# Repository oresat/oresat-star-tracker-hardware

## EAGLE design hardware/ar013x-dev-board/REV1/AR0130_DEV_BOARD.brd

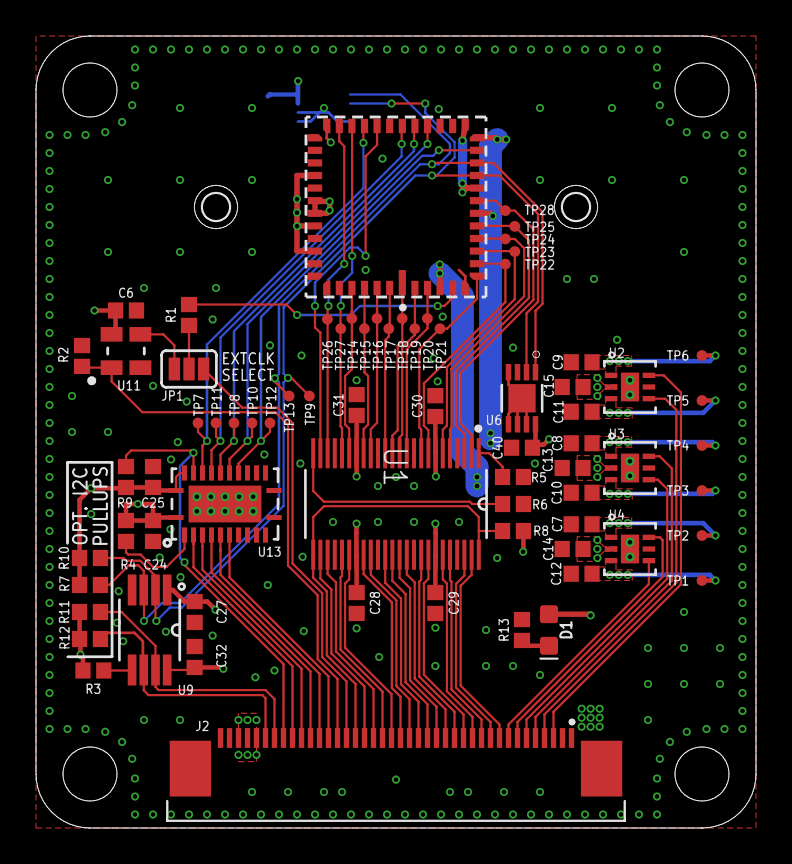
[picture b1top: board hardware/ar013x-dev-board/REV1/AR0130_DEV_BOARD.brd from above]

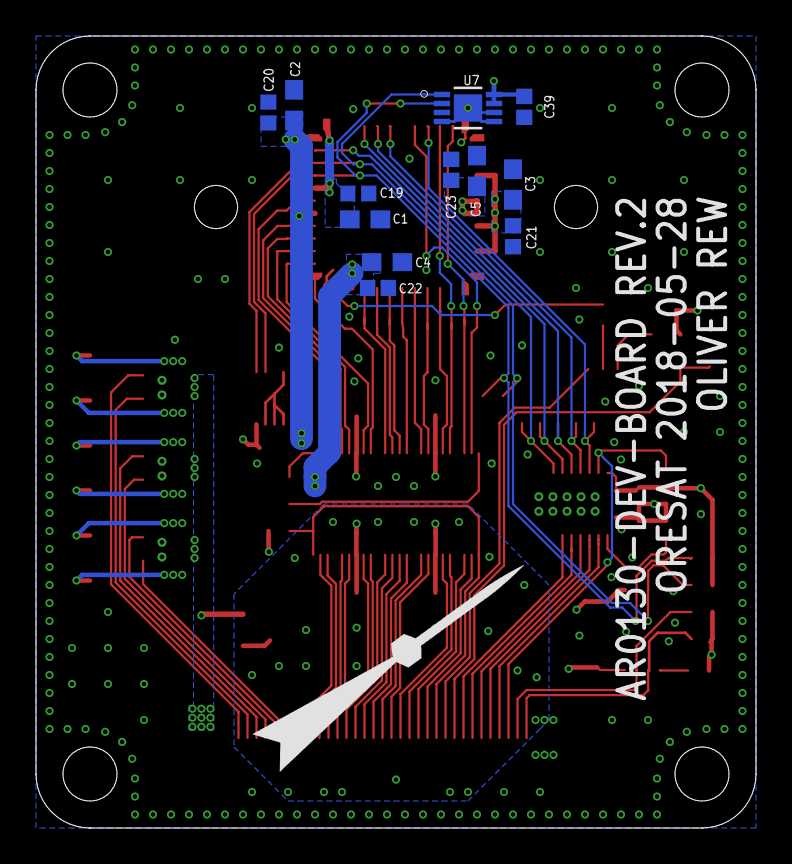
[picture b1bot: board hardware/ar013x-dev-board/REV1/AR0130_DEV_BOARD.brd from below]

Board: 4 copper layers, 40.0 x 44.0 mm, 86 parts (13 on the bottom side), 72 nets.

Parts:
C1, C2, C3, C4, C5: 10uF; 0603
C6: 10nF; 0402
C7, C8, C9, C10, C11, C12, C13, C14, C15: 1.0uF; 0402
C19, C20, C21, C22, C23, C24, C25, C27, C28, C29, C30, C31, C32, C39, C40: 0.1uF; 0402
D1: LED-0603
J2: 4-1734592-04-1734592-0; TE_4-1734592-0
JP1: CLKSEL; SJ_3_PASTE1&2
R1: 100; 0402
R2, R3, R4, R5, R6, R7, R8, R9, R10, R11, R12: 10k; 0402
R13: 1k; 0402
TP1, TP2, TP3, TP4, TP5, TP6, TP7, TP8, TP9, TP10, TP11, TP12, TP13, TP14, TP15, TP16, TP17, TP18, TP19, TP20, TP21, TP22, TP23, TP24, TP25, TP26, TP27, TP28: TPTP06R; TP06R
U1: SN74AVCB164245VR; DGV48
U2, U3: TPS71928-28DRVT; DRV6_1P6X1
U4: TPS71818-33DRVT; DRV6_1P6X1
U6, U7: MCP9808T-E/MCDFN8_2X3MC-M; DFN8_2X3MC-M
U9: TCA9509DGKRDGK8-M; DGK8-M
U11: KC2520B27.0000C10E00; OSC_KYOCERA_KC2520B
U13: SN74AVCH8T245RHLR; RHL24_4P05X2P05
U$1: M12-LENS-MOUNT
U$2: AR0130CSSM00SPCA0−DRBR1-847AC-ILCC; AR0130CSSM00SPCA0−DRBR1-847AB
U$3: PSAS_LOGO_15X15

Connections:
1.8V: C1.1, C7.1, C19.1, TP2.TP, U4.1, U$2.14, U$2.19
2.8V: C2.1, C6.2, C8.1, C20.1, C25.1, C27.1, C30.1, C31.1, C39.1, C40.1, R7.2, R9.2, R10.1, TP4.TP, U1.7, U1.18, U3.1, U6.8, U7.7, U7.8, U9.1, U11.4, U13.23, U13.24, U$2.12, U$2.18
3.3V: C12.1, C24.1, C28.1, C29.1, C32.1, R3.2, R4.1, R8.2, R11.1, R12.2, TP1.TP, U1.31, U1.42, U4.3, U9.8, U13.1
3.3V_EN: J2.8, U4.4
5V: C13.1, C14.1, C15.1, D1.A, J2.36, J2.37, J2.38, U2.2, U3.2, U4.2
CLK_EN: J2.27, R2.2, U11.1
DE_0: J2.21, U1.30
DE_1: J2.20, U1.32
DE_2: J2.19, U1.33
DE_3: J2.18, U1.35
DE_4: J2.17, U1.36
DE_5: J2.16, U1.37
DE_6: J2.15, U1.38
DE_7: J2.14, U1.40
DE_8: J2.13, U1.41
DE_9: J2.12, U1.43
DE_10: J2.11, U1.44
DE_11: J2.10, U1.46
DI_0: TP14.TP, U1.19, U$2.45
DI_1: TP15.TP, U1.17, U$2.46
DI_2: TP16.TP, U1.16, U$2.47
DI_3: TP17.TP, U1.14, U$2.48
DI_4: TP18.TP, U1.13, U$2.1
DI_5: TP19.TP, U1.12, U$2.2
DI_6: TP20.TP, U1.11, U$2.3
DI_7: TP21.TP, U1.9, U$2.7
DI_8: TP22.TP, U1.8, U$2.8
DI_9: TP23.TP, U1.6, U$2.9
DI_10: TP24.TP, U1.5, U$2.10
DI_11: TP25.TP, U1.3, U$2.11
EXTCLK: JP1.2, R1.1
EXTCLK_E: J2.26, JP1.3
EXTCLK_I: JP1.1, U11.3
FLASH_E: J2.24, U1.26
FLASH_I: U1.23, U$2.26
GND: C1.2, C2.2, C3.2, C4.2, C5.2, C6.1, C7.2, C8.2, C9.2, C10.2, C11.2, C12.2, C13.2, C14.2, C15.2, C19.2, C20.2, C21.2, C22.2, C23.2, C24.2, C25.2, C27.2, C28.2, C29.2, C30.2, C31.2, C32.2, C39.2, C40.2, J2.1, J2.2, J2.39, J2.40, J2.S1, J2.S2, R2.1, R5.1, R6.1, R13.2, U1.4, U1.10, U1.15, U1.21, U1.28, U1.34, U1.39, U1.45, U2.5, U2.7, U2.8, U2.9, U3.5, U3.7, U3.8, U3.9, U4.5, U4.7, U4.8, U4.9, U6.4, U6.5, U6.6, U6.7, U6.9, U7.4, U7.5, U7.6, U7.9, U9.4, U11.2, U13.11, U13.12, U13.13, U13.25, U13.P$1, U13.P$2, U13.P$3, U13.P$4, U13.P$5, U13.P$6, U13.P$7, U13.P$8, U13.P$9, U13.P$10, U$2.6, U$2.25, U$2.30, U$2.35, U$2.39, U$2.44
HSYNC_E: J2.23, U1.27
HSYNC_I: TP26.TP, U1.22, U$2.29
INPUT_DRVR_EN: J2.33, R9.1, U13.22
unnamed: R1.2, U$2.5
unnamed: D1.C, R13.1
unnamed: R5.2, U1.1
unnamed: R3.1, U9.5
unnamed: R4.2, U13.2
unnamed: R6.2, U1.24
OE_BAR_E: J2.30, U13.5
OE_BAR_I: TP8.TP, U13.19, U$2.23
OUTPUT_DRVR_EN: J2.25, R8.1, U1.25, U1.48
PIXCLK_E: J2.9, U1.47
PIXCLK_I: TP28.TP, U1.2, U$2.13
RST_BAR_E: J2.28, U13.7
RST_BAR_I: TP9.TP, U13.17, U$2.17
SADDR_E: J2.31, U13.4
SADDR_I: TP11.TP, U13.20, U$2.24
SCL_E: J2.34, R12.1, U9.7
SCL_I: R7.1, TP12.TP, U6.2, U7.2, U9.2, U$2.15
SDA_E: J2.35, R11.2, U9.6
SDA_I: R10.2, TP13.TP, U6.1, U7.1, U9.3, U$2.16
STANDBY_E: J2.29, U13.6
STANDBY_I: TP10.TP, U13.18, U$2.22
TRIG_E: J2.32, U13.3
TRIG_I: TP7.TP, U13.21, U$2.27
VAA_EN: J2.3, U2.6
VAA_PIX_EN: J2.4, U2.4
VCC: C3.1, C9.1, C21.1, TP6.TP, U2.1, U$2.34, U$2.38, U$2.40
VCC_1: C4.1, C10.1, C22.1, TP3.TP, U3.3, U$2.4
VCC_2: C5.1, C11.1, C23.1, TP5.TP, U2.3, U$2.36, U$2.37
VDD18_EN: J2.7, U4.6
VDD_IO_EN: J2.5, U3.6
VDD_PLL_EN: J2.6, U3.4
VSYNC_E: J2.22, U1.29
VSYNC_I: TP27.TP, U1.20, U$2.28

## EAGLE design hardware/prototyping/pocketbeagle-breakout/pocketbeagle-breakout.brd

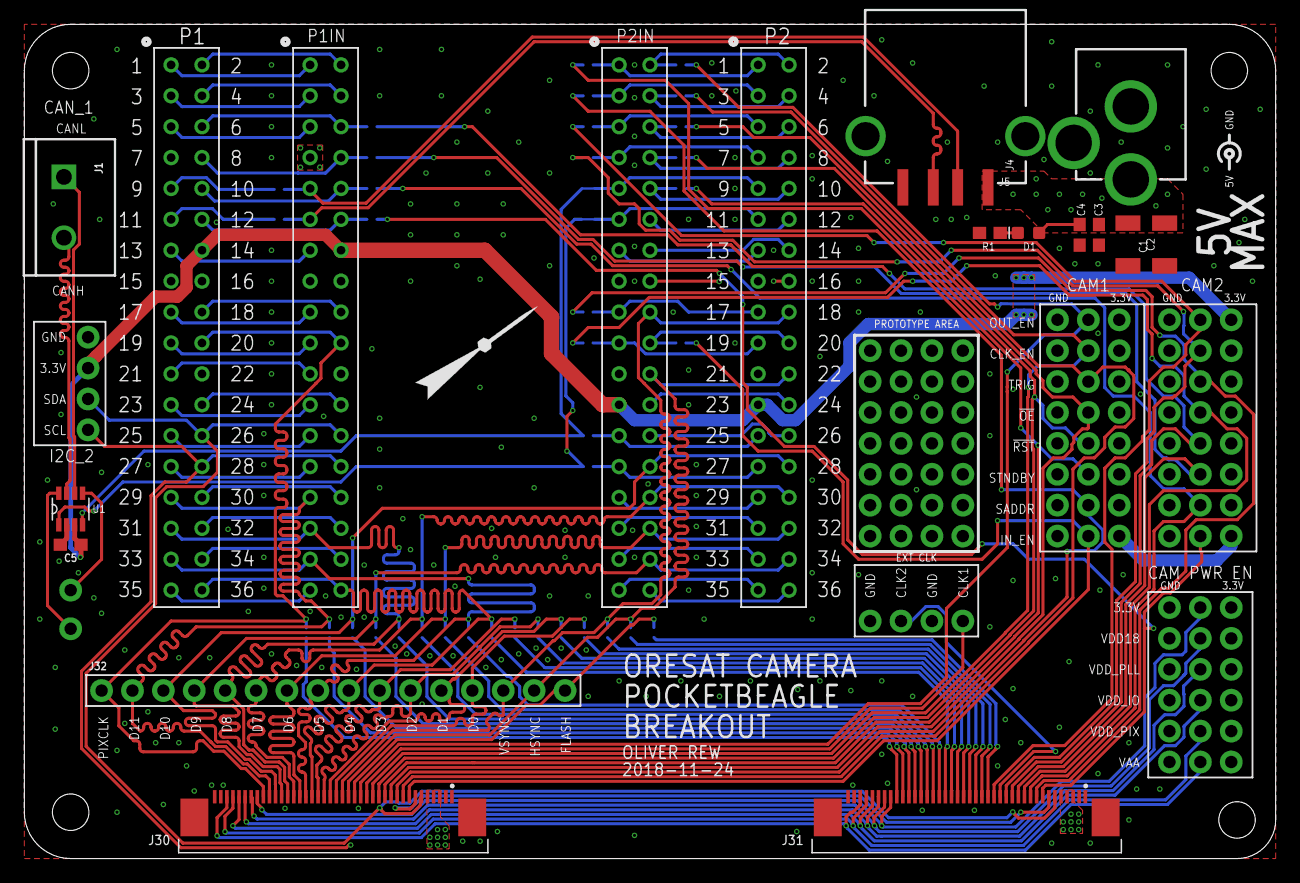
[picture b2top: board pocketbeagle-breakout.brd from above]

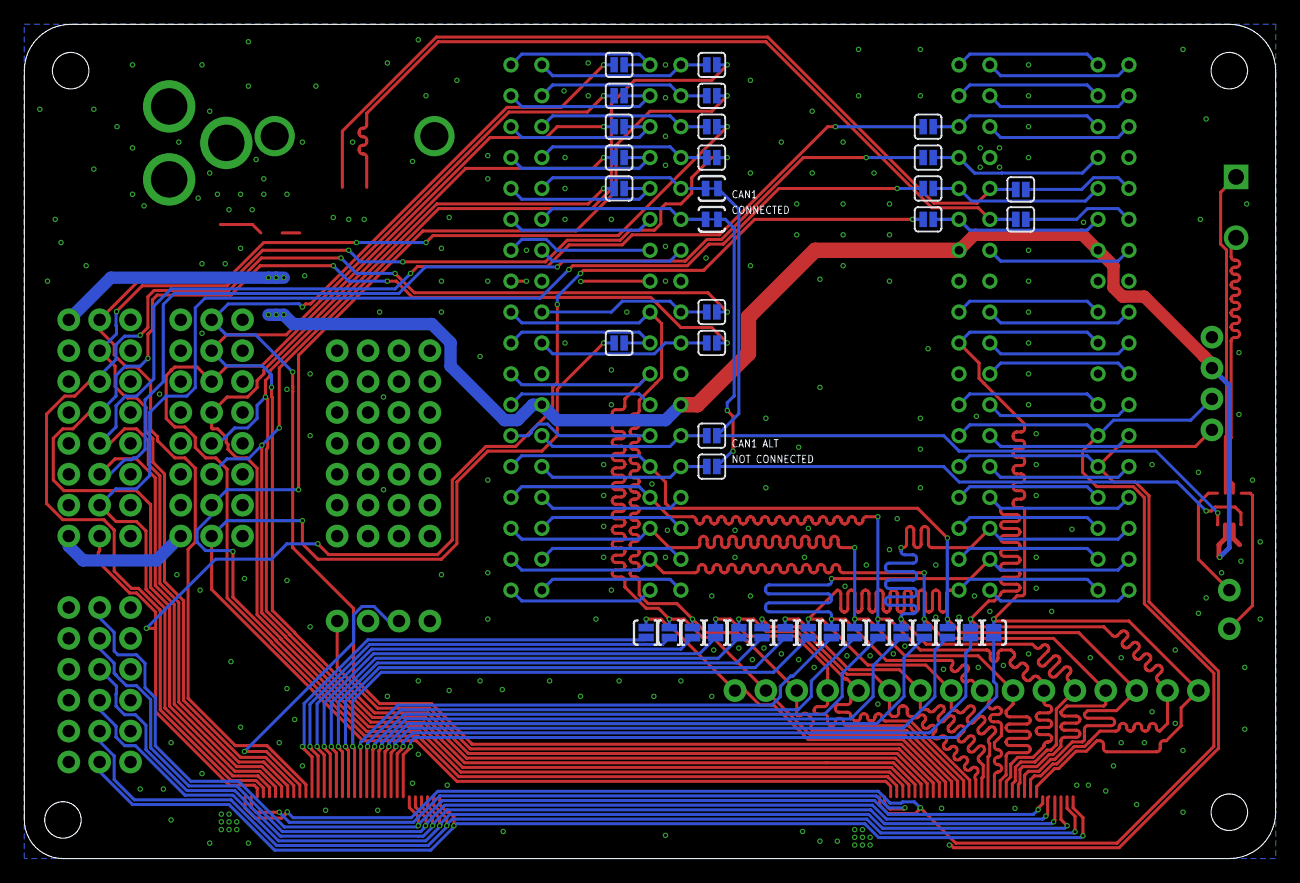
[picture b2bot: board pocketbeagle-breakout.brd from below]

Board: 4 copper layers, 102.9 x 68.6 mm, 91 parts (39 on the bottom side), 121 nets.

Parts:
C1, C2: 22UF; 1210
C3, C4, C5: 0.1uF; 0603
D1: GREEN; LED-0603
J1: SCREWTERMINAL-5MM-2
J3, J6, J7, J8, J9, J10, J11, J12, J13, J14, J15, J16, J17, J18, J20, J22, J23, J24, J25, J26, J27, J28: 1X03_NO_SILK
J4: USB_A_SMT_FEMALE; USB-A-S-SILK-FEMALE
J5: POWER_JACK; POWER_JACK_PTH
J19, J38, J39, J40, J41, J42, J43, J44, J45: 1X04_NO_SILK
J30, J31: 4-1734592-04-1734592-0; TE_4-1734592-0
J32: 1X16_NO_SILK
J36, J37: 1X01_NO_SILK
P1, P1IN, P2, P2IN: BCS-118-L-D-TE; CON36_2X18_TU_BCS
R1: 1k; 0603
SJ1, SJ2, SJ3, SJ4, SJ5, SJ6, SJ7, SJ8, SJ9, SJ10, SJ11, SJ12, SJ13, SJ14, SJ15, SJ16: SOLDERJUMPERNC2; SJ_2S-NOTRACE
SJ17, SJ18, SJ21, SJ22, SJ23, SJ24, SJ25, SJ26, SJ27, SJ28, SJ29, SJ30, SJ31, SJ32, SJ33, SJ34, SJ35, SJ36, SJ37, SJ38: SOLDERJUMPERNC; SJ_2S
SJ19, SJ20: SOLDERJUMPERTRACE; SJ_2S-TRACE
U1: TCAN330; SOT23-8_TI-DCN
U$1: PSAS_LOGO_10X10_NEW
U$2: POLARITY_SYMBOL_SMALL

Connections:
3.3V: C5.1, J3.3, J6.3, J7.3, J8.3, J9.3, J10.3, J11.3, J12.3, J13.3, J14.3, J15.3, J16.3, J17.3, J18.3, J19.2, J20.3, J22.3, J23.3, J24.3, J25.3, J26.3, J27.3, J28.3, P1.14, P1IN.14, P2.23, P2IN.23, U1.3
3.3V_EN: J17.2, J30.33, J31.33
5V: C1.1, C2.1, C3.1, C4.1, D1.A, J4.VBUS, J5.PWR, J30.3, J30.4, J30.5, J31.3, J31.4, J31.5, P1.7, P1IN.7
CAN_H: J1.2, U1.7
CAN_L: J1.1, U1.6
CAN_RX: SJ17.2, SJ19.2, U1.4
CAN_TX: SJ18.2, SJ20.2, U1.1
CLK_EN_1: J26.2, J30.14, SJ36.1
CLK_EN_2: J11.2, J31.14, SJ29.2
D0: J30.20, J32.13, SJ15.1
D1: J30.21, J32.12, SJ14.1
D2: J30.22, J32.11, SJ13.1
D3: J30.23, J32.10, SJ12.1
D4: J30.24, J32.9, P1.36, P1IN.36, SJ11.1
D5: J30.25, J32.8, P1.33, P1IN.33, SJ10.1
D6: J30.26, J32.7, P2.32, P2IN.32, SJ9.1
D7: J30.27, J32.6, P2.30, P2IN.30, SJ8.1
D8: J30.28, J32.5, P1.31, P1IN.31, SJ7.1
D9: J30.29, J32.4, P2.34, P2IN.34, SJ6.1
D10: J30.30, J32.3, P2.28, P2IN.28, SJ5.1
D11: J30.31, J32.2, P1.29, P1IN.29, SJ4.1
EXTCLK_1: J30.15, J38.4
EXTCLK_2: J31.15, J38.2
FLASH: J30.17, J32.16, SJ16.2
GND: C1.2, C2.2, C3.2, C4.2, C5.2, J3.1, J4.GND, J4.SHLD1, J4.SHLD2, J5.GND, J5.GNDBREAK, J6.1, J7.1, J8.1, J9.1, J10.1, J11.1, J12.1, J13.1, J14.1, J15.1, J16.1, J17.1, J18.1, J19.1, J20.1, J22.1, J23.1, J24.1, J25.1, J26.1, J27.1, J28.1, J30.1, J30.2, J30.39, J30.40, J30.S1, J30.S2, J31.1, J31.2, J31.39, J31.40, J31.S1, J31.S2, J38.1, J38.3, P1.15, P1.16, P1.22, P1IN.15, P1IN.16, P1IN.22, P2.15, P2.21, P2IN.15, P2IN.21, R1.2, U1.2
HSYNC: J30.18, J32.15, P2.22, P2IN.22, SJ3.1
INPUT_DRVR_EN_1: J27.2, J30.8, SJ35.2
INPUT_DRVR_EN_2: J18.2, J31.8, SJ33.1
unnamed: P2.2, P2IN.2, SJ34.1
unnamed: J31.17, SJ16.1
unnamed: J31.18, SJ3.2
unnamed: J31.19, SJ2.2
unnamed: J31.20, SJ15.2
unnamed: J31.21, SJ14.2
unnamed: J31.22, SJ13.2
unnamed: J31.23, SJ12.2
unnamed: J31.24, SJ11.2
unnamed: J31.25, SJ10.2
unnamed: J31.26, SJ9.2
unnamed: J31.27, SJ8.2
unnamed: J31.28, SJ7.2
unnamed: J31.29, SJ6.2
unnamed: J31.30, SJ5.2
unnamed: J31.31, SJ4.2
unnamed: J31.32, SJ1.2
unnamed: J36.1, U1.5
unnamed: J37.1, U1.8
unnamed: P2.9, P2IN.9, SJ19.1
unnamed: P2.11, P2IN.11, SJ20.1
unnamed: P2.25, P2IN.25, SJ17.1
unnamed: P2.27, P2IN.27, SJ18.1
unnamed: D1.C, R1.1
unnamed: P2.1, P2IN.1, SJ22.2
unnamed: P2.10, P2IN.10, SJ23.2
unnamed: P2.8, P2IN.8, SJ24.2
unnamed: P2.6, P2IN.6, SJ25.2
unnamed: P2.17, P2IN.17, SJ26.1
unnamed: P2.19, P2IN.19, SJ27.1
unnamed: P2.5, P2IN.5, SJ28.1
unnamed: P2.7, P2IN.7, SJ29.1
unnamed: P1.12, P1IN.12, SJ33.2
unnamed: P1.10, P1IN.10, SJ32.2
unnamed: P1.8, P1IN.8, SJ31.2
unnamed: P1.6, P1IN.6, SJ30.2
unnamed: P2.20, P2IN.20, SJ35.1
unnamed: P2.4, P2IN.4, SJ36.2
unnamed: P1.9, SJ37.1
unnamed: P1.11, SJ38.1
unnamed: P1.27, P1IN.27
unnamed: P1.25, P1IN.25
unnamed: P1.23, P1IN.23
unnamed: P1.21, P1IN.21
unnamed: P1.19, P1IN.19
unnamed: P1.17, P1IN.17
unnamed: P1.13, P1IN.13
unnamed: P1.5, P1IN.5
unnamed: P1.3, P1IN.3
unnamed: P1.1, P1IN.1
unnamed: P1.35, P1IN.35
unnamed: P1.34, P1IN.34
unnamed: P1.32, P1IN.32
unnamed: P1.30, P1IN.30
unnamed: P1.24, P1IN.24
unnamed: P1.18, P1IN.18
unnamed: P1.4, P1IN.4
unnamed: P2.3, P2IN.3, SJ21.2
unnamed: P1.2, P1IN.2
unnamed: P2.13, P2IN.13
unnamed: P2.29, P2IN.29
unnamed: P2.31, P2IN.31
unnamed: P2.33, P2IN.33
unnamed: P2.35, P2IN.35
unnamed: P2.12, P2IN.12
unnamed: P2.14, P2IN.14
unnamed: P2.16, P2IN.16
unnamed: P2.24, P2IN.24
unnamed: P2.26, P2IN.26
unnamed: P2.36, P2IN.36
OE_BAR_1: J24.2, J30.11, SJ24.1
OE_BAR_2: J9.2, J31.11, SJ27.2
OUTPUT_DRVR_EN_1: J28.2, J30.16, SJ34.2
OUTPUT_DRVR_EN_2: J20.2, J31.16, SJ28.2
PIXCLK: J30.32, J32.1, P1.20, P1IN.20, SJ1.1
RST_BAR_1: J23.2, J30.13, SJ23.1
RST_BAR_2: J8.2, J31.13, SJ30.1
SADDR_1: J3.2, J30.10, SJ21.1
SADDR_2: J6.2, J31.10, SJ32.1
SCL2: J19.4, J30.7, J31.7, P1.28, P1IN.28
SDA2: J19.3, J30.6, J31.6, P1.26, P1IN.26
STANDBY_1: J22.2, J30.12, SJ22.1
STANDBY_2: J7.2, J31.12, SJ31.1
TRIG_1: J25.2, J30.9, SJ25.1
TRIG_2: J10.2, J31.9, SJ26.2
USB_D+: J4.D+, P1IN.11, SJ38.2
USB_D-: J4.D-, P1IN.9, SJ37.2
VAA_EN: J12.2, J30.38, J31.38
VDD18_EN: J16.2, J30.34, J31.34
VDD_IO_EN: J14.2, J30.36, J31.36
VDD_PIX_EN: J13.2, J30.37, J31.37
VDD_PLL_EN: J15.2, J30.35, J31.35
VSYNC: J30.19, J32.14, P2.18, P2IN.18, SJ2.1

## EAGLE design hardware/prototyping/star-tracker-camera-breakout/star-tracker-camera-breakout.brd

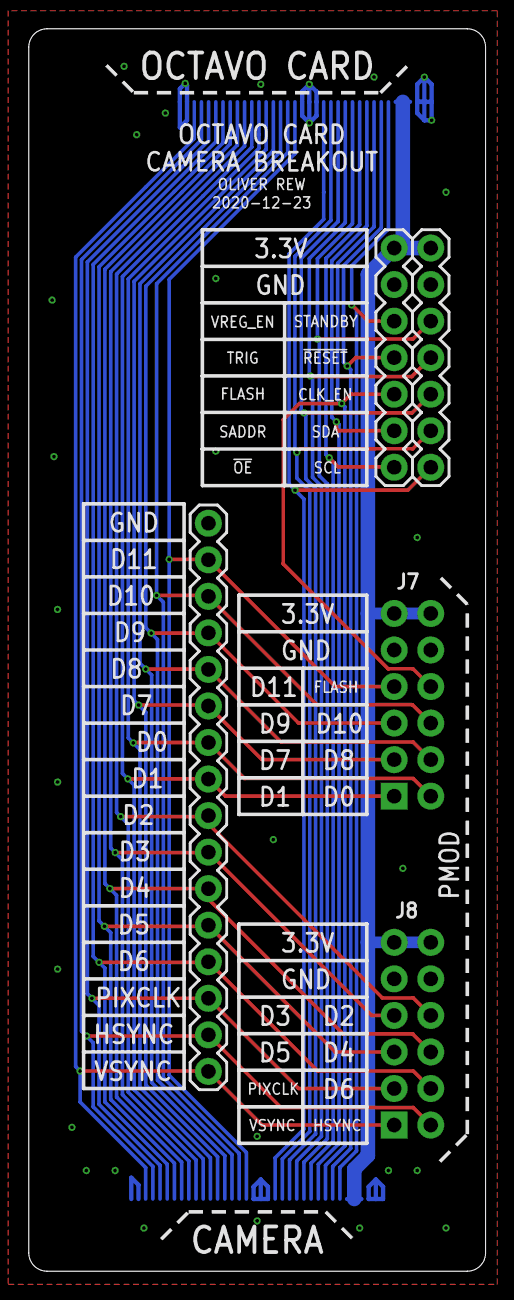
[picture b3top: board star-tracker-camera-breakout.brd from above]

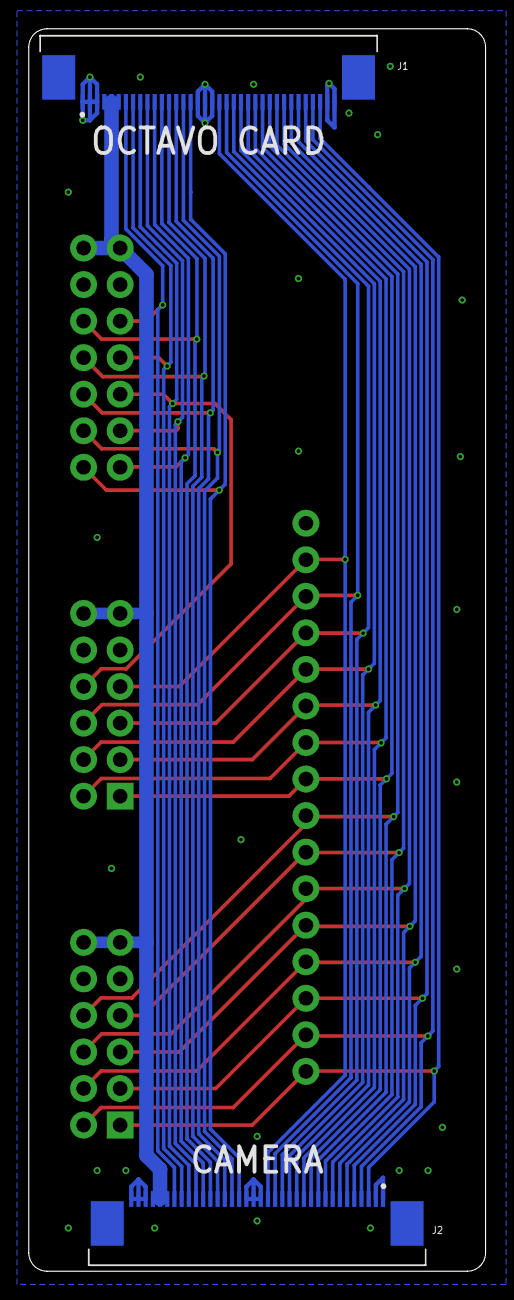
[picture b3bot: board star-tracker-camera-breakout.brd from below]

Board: 2 copper layers, 31.8 x 86.4 mm, 7 parts (2 on the bottom side), 27 nets.

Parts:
J1, J2: 3-1734592-64-1734592-0; TE_3-1734592-6
J3: 1X16
J4, J5: 1X07
J7, J8: 2X6 FEMALE; PMOD_PERIPH

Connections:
3.3V: J1.4, J1.5, J1.6, J2.31, J2.32, J2.33, J4.1, J5.1, J7.6, J7.12, J8.6, J8.12
!OE_E: J1.11, J2.26, J5.7
!RESET_E: J1.13, J2.24, J4.4
CLK_EN_E: J1.14, J2.23, J4.5
D0_E: J1.25, J2.12, J3.10, J7.7
D1_E: J1.26, J2.11, J3.9, J7.1
D2_E: J1.27, J2.10, J3.8, J8.10
D3_E: J1.28, J2.9, J3.7, J8.4
D4_E: J1.29, J2.8, J3.6, J8.9
D5_E: J1.30, J2.7, J3.5, J8.3
D6_E: J1.31, J2.6, J3.4, J8.8
D7_E: J1.24, J2.13, J3.11, J7.2
D8_E: J1.23, J2.14, J3.12, J7.8
D9_E: J1.22, J2.15, J3.13, J7.3
D10_E: J1.21, J2.16, J3.14, J7.9
D11_E: J1.20, J2.17, J3.15, J7.4
FLASH_E: J1.9, J2.28, J5.5, J7.10
GND: J1.1, J1.2, J1.3, J1.17, J1.18, J1.19, J1.35, J1.36, J1.S1, J1.S2, J2.1, J2.2, J2.18, J2.19, J2.20, J2.34, J2.35, J2.36, J2.S1, J2.S2, J3.16, J4.2, J5.2, J7.5, J7.11, J8.5, J8.11
HSYNC_E: J1.33, J2.4, J3.2, J8.7
I2C2_SCL: J1.16, J2.21, J4.7
I2C2_SDA: J1.15, J2.22, J4.6
PIXCLK_E: J1.32, J2.5, J3.3, J8.2
SADDR_E: J1.10, J2.27, J5.6
STANDBY_E: J1.12, J2.25, J4.3
TRIGGER_E: J1.8, J2.29, J5.4
VREG_EN_E: J1.7, J2.30, J5.3
VSYNC_E: J1.34, J2.3, J3.1, J8.1

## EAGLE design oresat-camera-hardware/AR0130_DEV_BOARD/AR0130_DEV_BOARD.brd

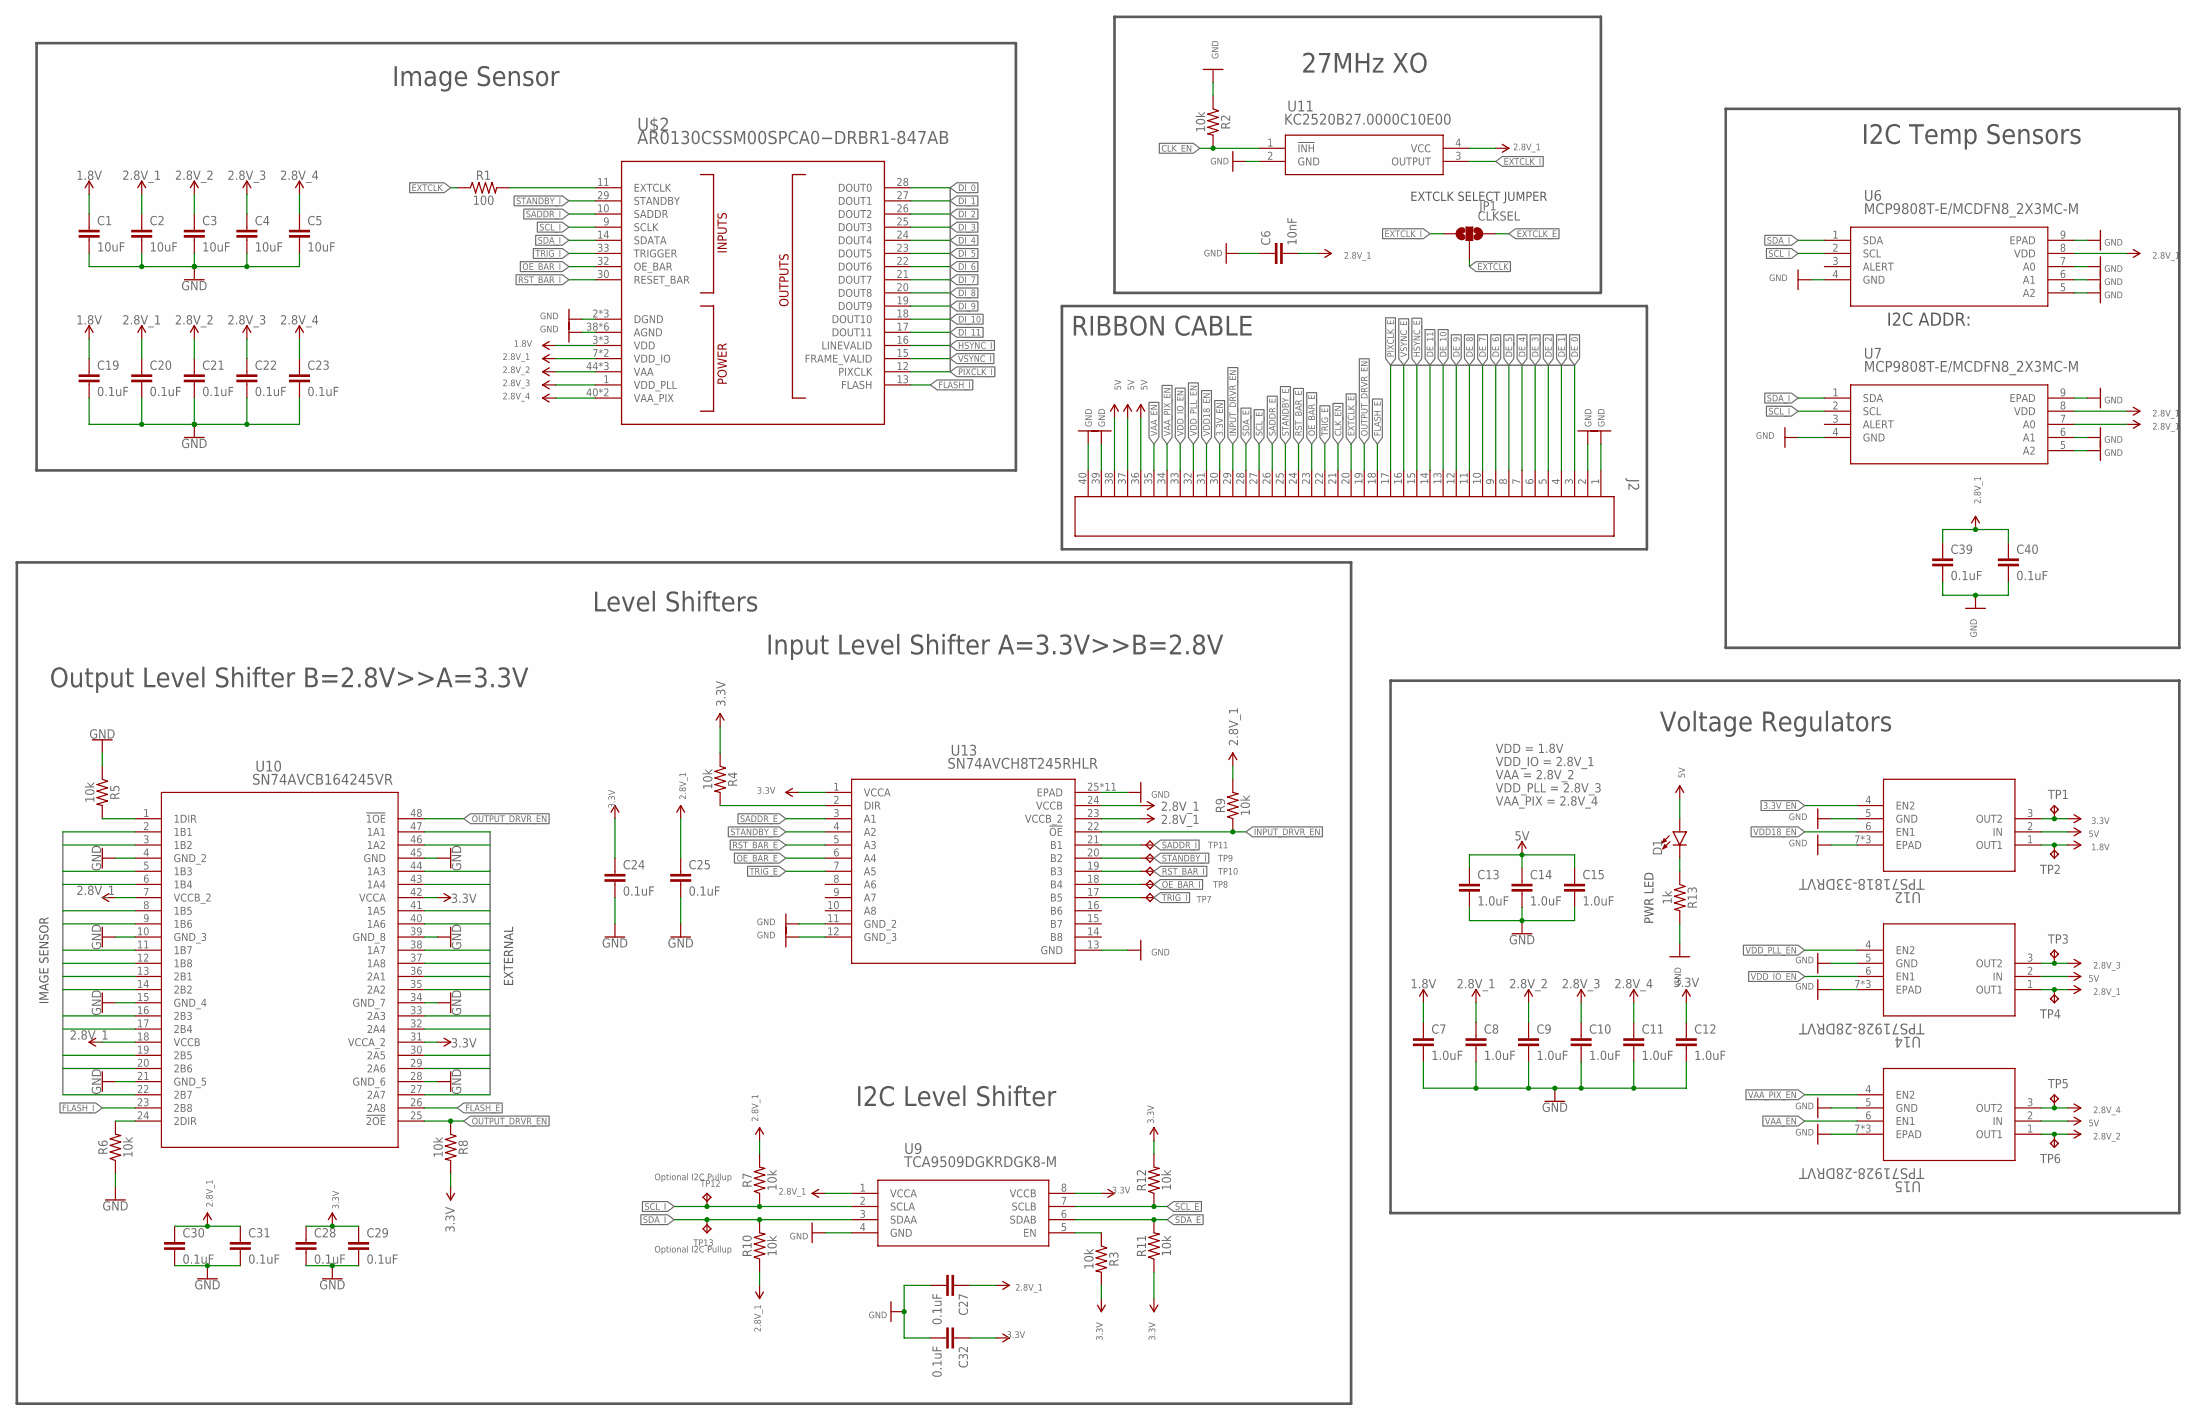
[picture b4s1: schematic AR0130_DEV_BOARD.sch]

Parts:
C1, C2, C3, C4, C5: 10uF; 0603
C6: 10nF; 0402
C7, C8, C9, C10, C11, C12, C13, C14, C15: 1.0uF; 0402
C19, C20, C21, C22, C23, C24, C25, C27, C28, C29, C30, C31, C32, C39, C40: 0.1uF; 0402
D1: LED0603; LED-0603
J2: 4-1734592-0; CONN_4-1734592-0_TYCO
JP1: CLKSEL; SJ_3_PASTE1&2
R1: 100; 0402
R2, R3, R4, R5, R6, R7, R8, R9, R10, R11, R12: 10k; 0402
R13: 1k; 0402
TP1, TP2, TP3, TP4, TP5, TP6, TP7, TP8, TP9, TP10, TP11, TP12, TP13: TPTP06R; TP06R
U6, U7: MCP9808T-E/MCDFN8_2X3MC-M; DFN8_2X3MC-M
U9: TCA9509DGKRDGK8-M; DGK8-M
U10: SN74AVCB164245VR; DGV48
U11: KC2520B27.0000C10E00; OSC_KYOCERA_KC2520B
U12: TPS71818-33DRVT; DRV6_1P6X1
U13: SN74AVCH8T245RHLR; RHL24_4P05X2P05
U14, U15: TPS71928-28DRVT; DRV6_1P6X1
U$2: AR0130CSSM00SPCA0−DRBR1-847AB

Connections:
1.8V: C1.1, C7.1, C19.1, TP2.TP, U12.1 (OUT1), U$2.3 (VDD), U$2.4 (VDD), U$2.34 (VDD)
2.8V: C2.1, C6.2, C8.1, C20.1, C25.1, C27.1, C30.1, C31.1, C39.1, C40.1, R7.2, R9.2, R10.1, TP4.TP, U6.8 (VDD), U7.7 (A0), U7.8 (VDD), U9.1 (VCCA), U10.7 (VCCB_2), U10.18 (VCCB), U11.4 (VCC), U13.23 (VCCB_2), U13.24 (VCCB), U14.1 (OUT1), U$2.7 (VDD_IO), U$2.8 (VDD_IO)
3.3V: C12.1, C24.1, C28.1, C29.1, C32.1, R3.2, R4.1, R8.2, R11.1, R12.2, TP1.TP, U9.8 (VCCB), U10.31 (VCCA_2), U10.42 (VCCA), U12.3 (OUT2), U13.1 (VCCA)
3.3V_EN: J2.30, U12.4 (EN2)
5V: C13.1, C14.1, C15.1, D1.A, J2.36, J2.37, J2.38, U12.2 (IN), U14.2 (IN), U15.2 (IN)
CLK_EN: J2.21, R2.2, U11.1 (!INH)
DE_0: J2.3, U10.47 (1A1)
DE_1: J2.4, U10.46 (1A2)
DE_2: J2.5, U10.44 (1A3)
DE_3: J2.6, U10.43 (1A4)
DE_4: J2.7, U10.41 (1A5)
DE_5: J2.8, U10.40 (1A6)
DE_6: J2.9, U10.38 (1A7)
DE_7: J2.10, U10.37 (1A8)
DE_8: J2.11, U10.36 (2A1)
DE_9: J2.12, U10.35 (2A2)
DE_10: J2.13, U10.33 (2A3)
DE_11: J2.14, U10.32 (2A4)
DI_0: U10.2 (1B1), U$2.28 (DOUT0)
DI_1: U10.3 (1B2), U$2.27 (DOUT1)
DI_2: U10.5 (1B3), U$2.26 (DOUT2)
DI_3: U10.6 (1B4), U$2.25 (DOUT3)
DI_4: U10.8 (1B5), U$2.24 (DOUT4)
DI_5: U10.9 (1B6), U$2.23 (DOUT5)
DI_6: U10.11 (1B7), U$2.22 (DOUT6)
DI_7: U10.12 (1B8), U$2.21 (DOUT7)
DI_8: U10.13 (2B1), U$2.20 (DOUT8)
DI_9: U10.14 (2B2), U$2.19 (DOUT9)
DI_10: U10.16 (2B3), U$2.18 (DOUT10)
DI_11: U10.17 (2B4), U$2.17 (DOUT11)
EXTCLK: JP1.2, R1.1
EXTCLK_E: J2.20, JP1.3
EXTCLK_I: JP1.1, U11.3 (OUTPUT)
FLASH_E: J2.18, U10.26 (2A8)
FLASH_I: U10.23 (2B8), U$2.13 (FLASH)
GND: C1.2, C2.2, C3.2, C4.2, C5.2, C6.1, C7.2, C8.2, C9.2, C10.2, C11.2, C12.2, C13.2, C14.2, C15.2, C19.2, C20.2, C21.2, C22.2, C23.2, C24.2, C25.2, C27.2, C28.2, C29.2, C30.2, C31.2, C32.2, C39.2, C40.2, J2.1, J2.2, J2.39, J2.40, R2.1, R5.1, R6.1, R13.2, U6.4 (GND), U6.5 (A2), U6.6 (A1), U6.7 (A0), U6.9 (EPAD), U7.4 (GND), U7.5 (A2), U7.6 (A1), U7.9 (EPAD), U9.4 (GND), U10.4 (GND_2), U10.10 (GND_3), U10.15 (GND_4), U10.21 (GND_5), U10.28 (GND_6), U10.34 (GND_7), U10.39 (GND_8), U10.45 (GND), U11.2 (GND), U12.5 (GND), U12.7 (EPAD), U12.8 (EPAD), U12.9 (EPAD), U13.11 (GND_2), U13.12 (GND_3), U13.13 (GND), U13.25 (EPAD), U13.P$1 (EPAD), U13.P$2 (EPAD), U13.P$3 (EPAD), U13.P$4 (EPAD), U13.P$5 (EPAD), U13.P$6 (EPAD), U13.P$7 (EPAD), U13.P$8 (EPAD), U13.P$9 (EPAD), U13.P$10 (EPAD), U14.5 (GND), U14.7 (EPAD), U14.8 (EPAD), U14.9 (EPAD), U15.5 (GND), U15.7 (EPAD), U15.8 (EPAD), U15.9 (EPAD), U$2.2 (DGND), U$2.5 (DGND), U$2.6 (DGND), U$2.38 (AGND), U$2.39 (AGND), U$2.42 (AGND), U$2.43 (AGND), U$2.47 (AGND), U$2.48 (AGND)
HSYNC_E: J2.15, U10.30 (2A5)
HSYNC_I: U10.19 (2B5), U$2.16 (LINEVALID)
INPUT_DRVR_EN: J2.29, R9.1, U13.22 (!OE)
unnamed: R1.2, U$2.11 (EXTCLK)
unnamed: D1.C, R13.1
unnamed: R5.2, U10.1 (1DIR)
unnamed: R3.1, U9.5 (EN)
unnamed: R4.2, U13.2 (DIR)
unnamed: R6.2, U10.24 (2DIR)
OE_BAR_E: J2.23, U13.6 (A4)
OE_BAR_I: TP8.TP, U13.18 (B4), U$2.32 (OE_BAR)
OUTPUT_DRVR_EN: J2.19, R8.1, U10.25 (!2OE), U10.48 (!1OE)
PIXCLK_E: J2.17, U10.27 (2A7)
PIXCLK_I: U10.22 (2B7), U$2.12 (PIXCLK)
RST_BAR_E: J2.24, U13.5 (A3)
RST_BAR_I: TP9.TP, U13.19 (B3), U$2.30 (RESET_BAR)
SADDR_E: J2.26, U13.3 (A1)
SADDR_I: TP11.TP, U13.21 (B1), U$2.10 (SADDR)
SCL_E: J2.27, R12.1, U9.7 (SCLB)
SCL_I: R7.1, TP12.TP, U6.2 (SCL), U7.2 (SCL), U9.2 (SCLA), U$2.9 (SCLK)
SDA_E: J2.28, R11.2, U9.6 (SDAB)
SDA_I: R10.2, TP13.TP, U6.1 (SDA), U7.1 (SDA), U9.3 (SDAA), U$2.14 (SDATA)
STANDBY_E: J2.25, U13.4 (A2)
STANDBY_I: TP10.TP, U13.20 (B2), U$2.29 (STANDBY)
TRIG_E: J2.22, U13.7 (A5)
TRIG_I: TP7.TP, U13.17 (B5), U$2.33 (TRIGGER)
VAA_EN: J2.35, U15.6 (EN1)
VAA_PIX_EN: J2.34, U15.4 (EN2)
VCC: C3.1, C9.1, C21.1, TP6.TP, U15.1 (OUT1), U$2.44 (VAA), U$2.45 (VAA), U$2.46 (VAA)
VCC_1: C4.1, C10.1, C22.1, TP3.TP, U14.3 (OUT2), U$2.1 (VDD_PLL)
VCC_2: C5.1, C11.1, C23.1, TP5.TP, U15.3 (OUT2), U$2.40 (VAA_PIX), U$2.41 (VAA_PIX)
VDD18_EN: J2.31, U12.6 (EN1)
VDD_IO_EN: J2.33, U14.6 (EN1)
VDD_PLL_EN: J2.32, U14.4 (EN2)
VSYNC_E: J2.16, U10.29 (2A6)
VSYNC_I: U10.20 (2B6), U$2.15 (FRAME_VALID)

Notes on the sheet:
I2C Temp Sensors
I2C Level Shifter
Voltage Regulators
Image Sensor
Output Level Shifter B=2.8V>>A=3.3V
27MHz XO
Input Level Shifter A=3.3V>>B=2.8V
Level Shifters
VDD_IO = 2.8V_1
Optional I2C Pullup
VDD = 1.8V
VDD_PLL = 2.8V_3
VAA = 2.8V_2
VAA_PIX = 2.8V_4
EXTCLK SELECT JUMPER
RIBBON CABLE
IMAGE SENSOR
EXTERNAL
PWR LED
I2C ADDR:

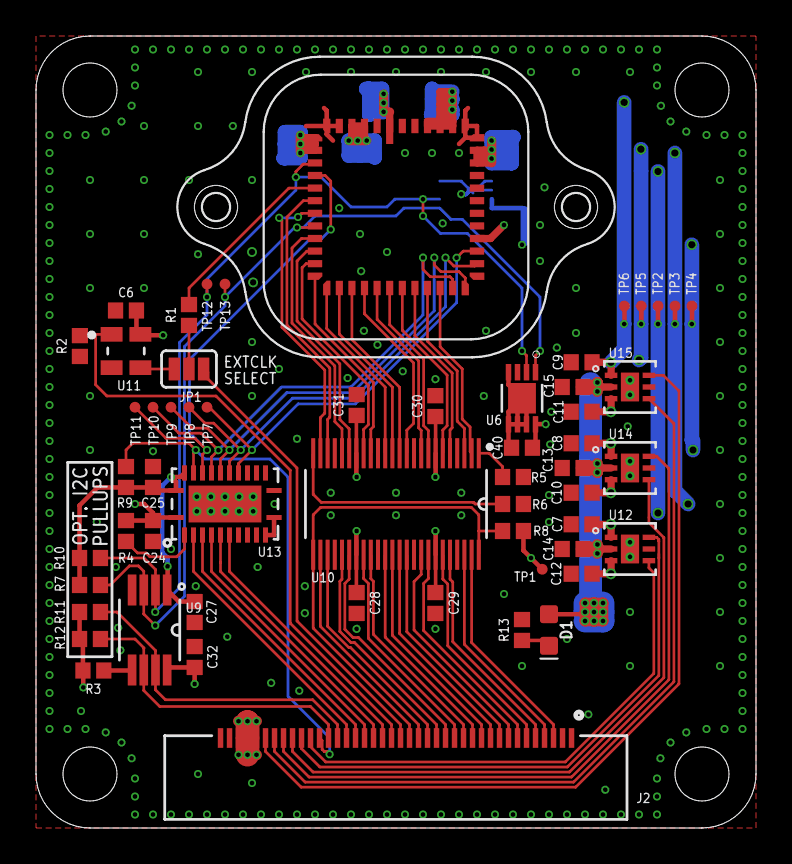
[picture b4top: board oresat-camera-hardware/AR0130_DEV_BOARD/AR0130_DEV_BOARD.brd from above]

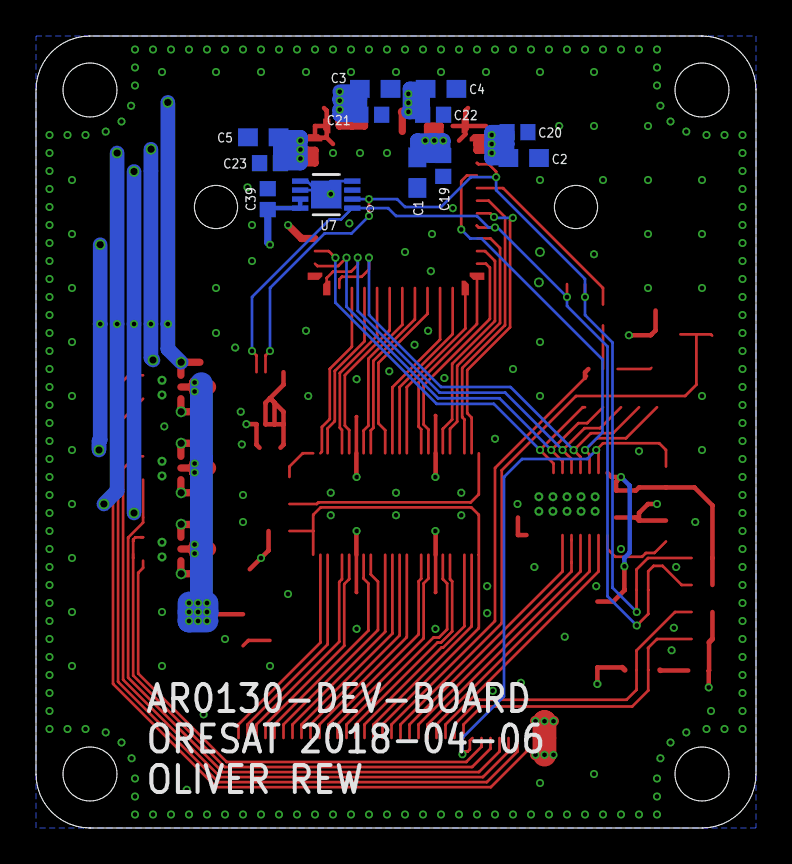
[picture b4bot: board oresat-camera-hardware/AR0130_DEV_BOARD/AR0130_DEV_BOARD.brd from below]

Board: 4 copper layers, 40.0 x 44.0 mm, 70 parts (12 on the bottom side), 72 nets.

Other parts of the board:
U$1: M12-LENS-MOUNT

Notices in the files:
parts and their libraries:
SparkFun-Resistors: Licensing: Creative Commons ShareAlike 4.0 International - https://creativecommons.org/licenses/by-sa/4.0
SparkFun-Passives: Licensing: CC v3.0 Share-Alike You are welcome to use this library for commercial purposes.
